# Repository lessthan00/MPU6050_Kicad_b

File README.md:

# MPU6050_Kicad

MPU6050模块Kicad PCB工程文件

更改自 https://github.com/letanga/MPU6050_Kicad

并未做太多调整
只是MPU6050的符号做了补充和完善.
同时转为kicad9版本, 再解决了转化后的错误.

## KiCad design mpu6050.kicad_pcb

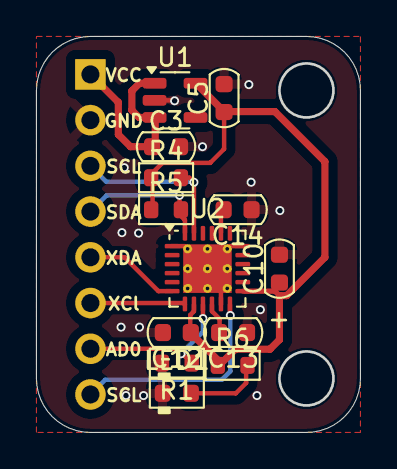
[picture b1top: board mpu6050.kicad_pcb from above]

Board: 2 copper layers, 18.0 x 22.0 mm, 14 parts (1 on the bottom side), 12 nets.

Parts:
C3, C10: 10uF; C_0603_1608Metric
C5, C12, C13: 100nF; C_0603_1608Metric
C14: 2.2nF; C_0603_1608Metric
J1: Conn_01x08; PinHeader_1x08_P2.54mm_Vertical
LED1: LED_0603; LED_0603_1608Metric
R1, R4, R5: 4.7K; R_0603_1608Metric
R6: 10K; R_0603_1608Metric
U1: SPX3819M5-L-3-3; SOT-23-5
U2: MPU-6050; QFN-24-1EP_4x4mm_P0.5mm_EP2.7x2.7mm_ThermalVias

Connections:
+3.3V: C5.1, C10.1, C12.1, R4.1, R5.1, R6.1, U1.5 (OUT), U2.8 (VDDIO), U2.13 (VDD)
+5V: C3.1, J1.1, U1.1 (IN), U1.3 (EN)
/AD0: J1.7, R1.1, U2.9 (AD0)
/INT: J1.8, U2.12 (INT)
/SCL: J1.3, R4.2, U2.23 (SCL)
/SDA: J1.4, R5.2, U2.24 (SDA)
/XCL: J1.6, U2.7 (AUX_SCL)
/XDA: J1.5, U2.6 (AUX_SDA)
GND: C3.2, C5.2, C10.2, C12.2, C13.1, C14.1, J1.2, LED1.1 (K), R1.2, U1.2 (GND), U2.1 (CLKIN), U2.11 (FSYNC), U2.18 (GND), U2.25 (GND)
unnamed: LED1.2 (A), R6.2
unnamed: C14.2, U2.20 (CPOUT)
unnamed: C13.2, U2.10 (REGOUT)
